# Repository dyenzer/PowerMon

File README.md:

#Power Monitor
Non-intrusive way to monitor the power consumed in your home

This repository contains the schematics and code for this project.
More details at https://hackaday.io/project/6700-home-power-usage-monitor
  
#Repository Contents
* **/Schematic** - Circuit diagram and PCB layout
  
#License Information
This project is released under <a href = "https://creativecommons.org/licenses/by-sa/4.0/">CC BY-SA 4.0</a>  
Original Design by Drew Yenzer

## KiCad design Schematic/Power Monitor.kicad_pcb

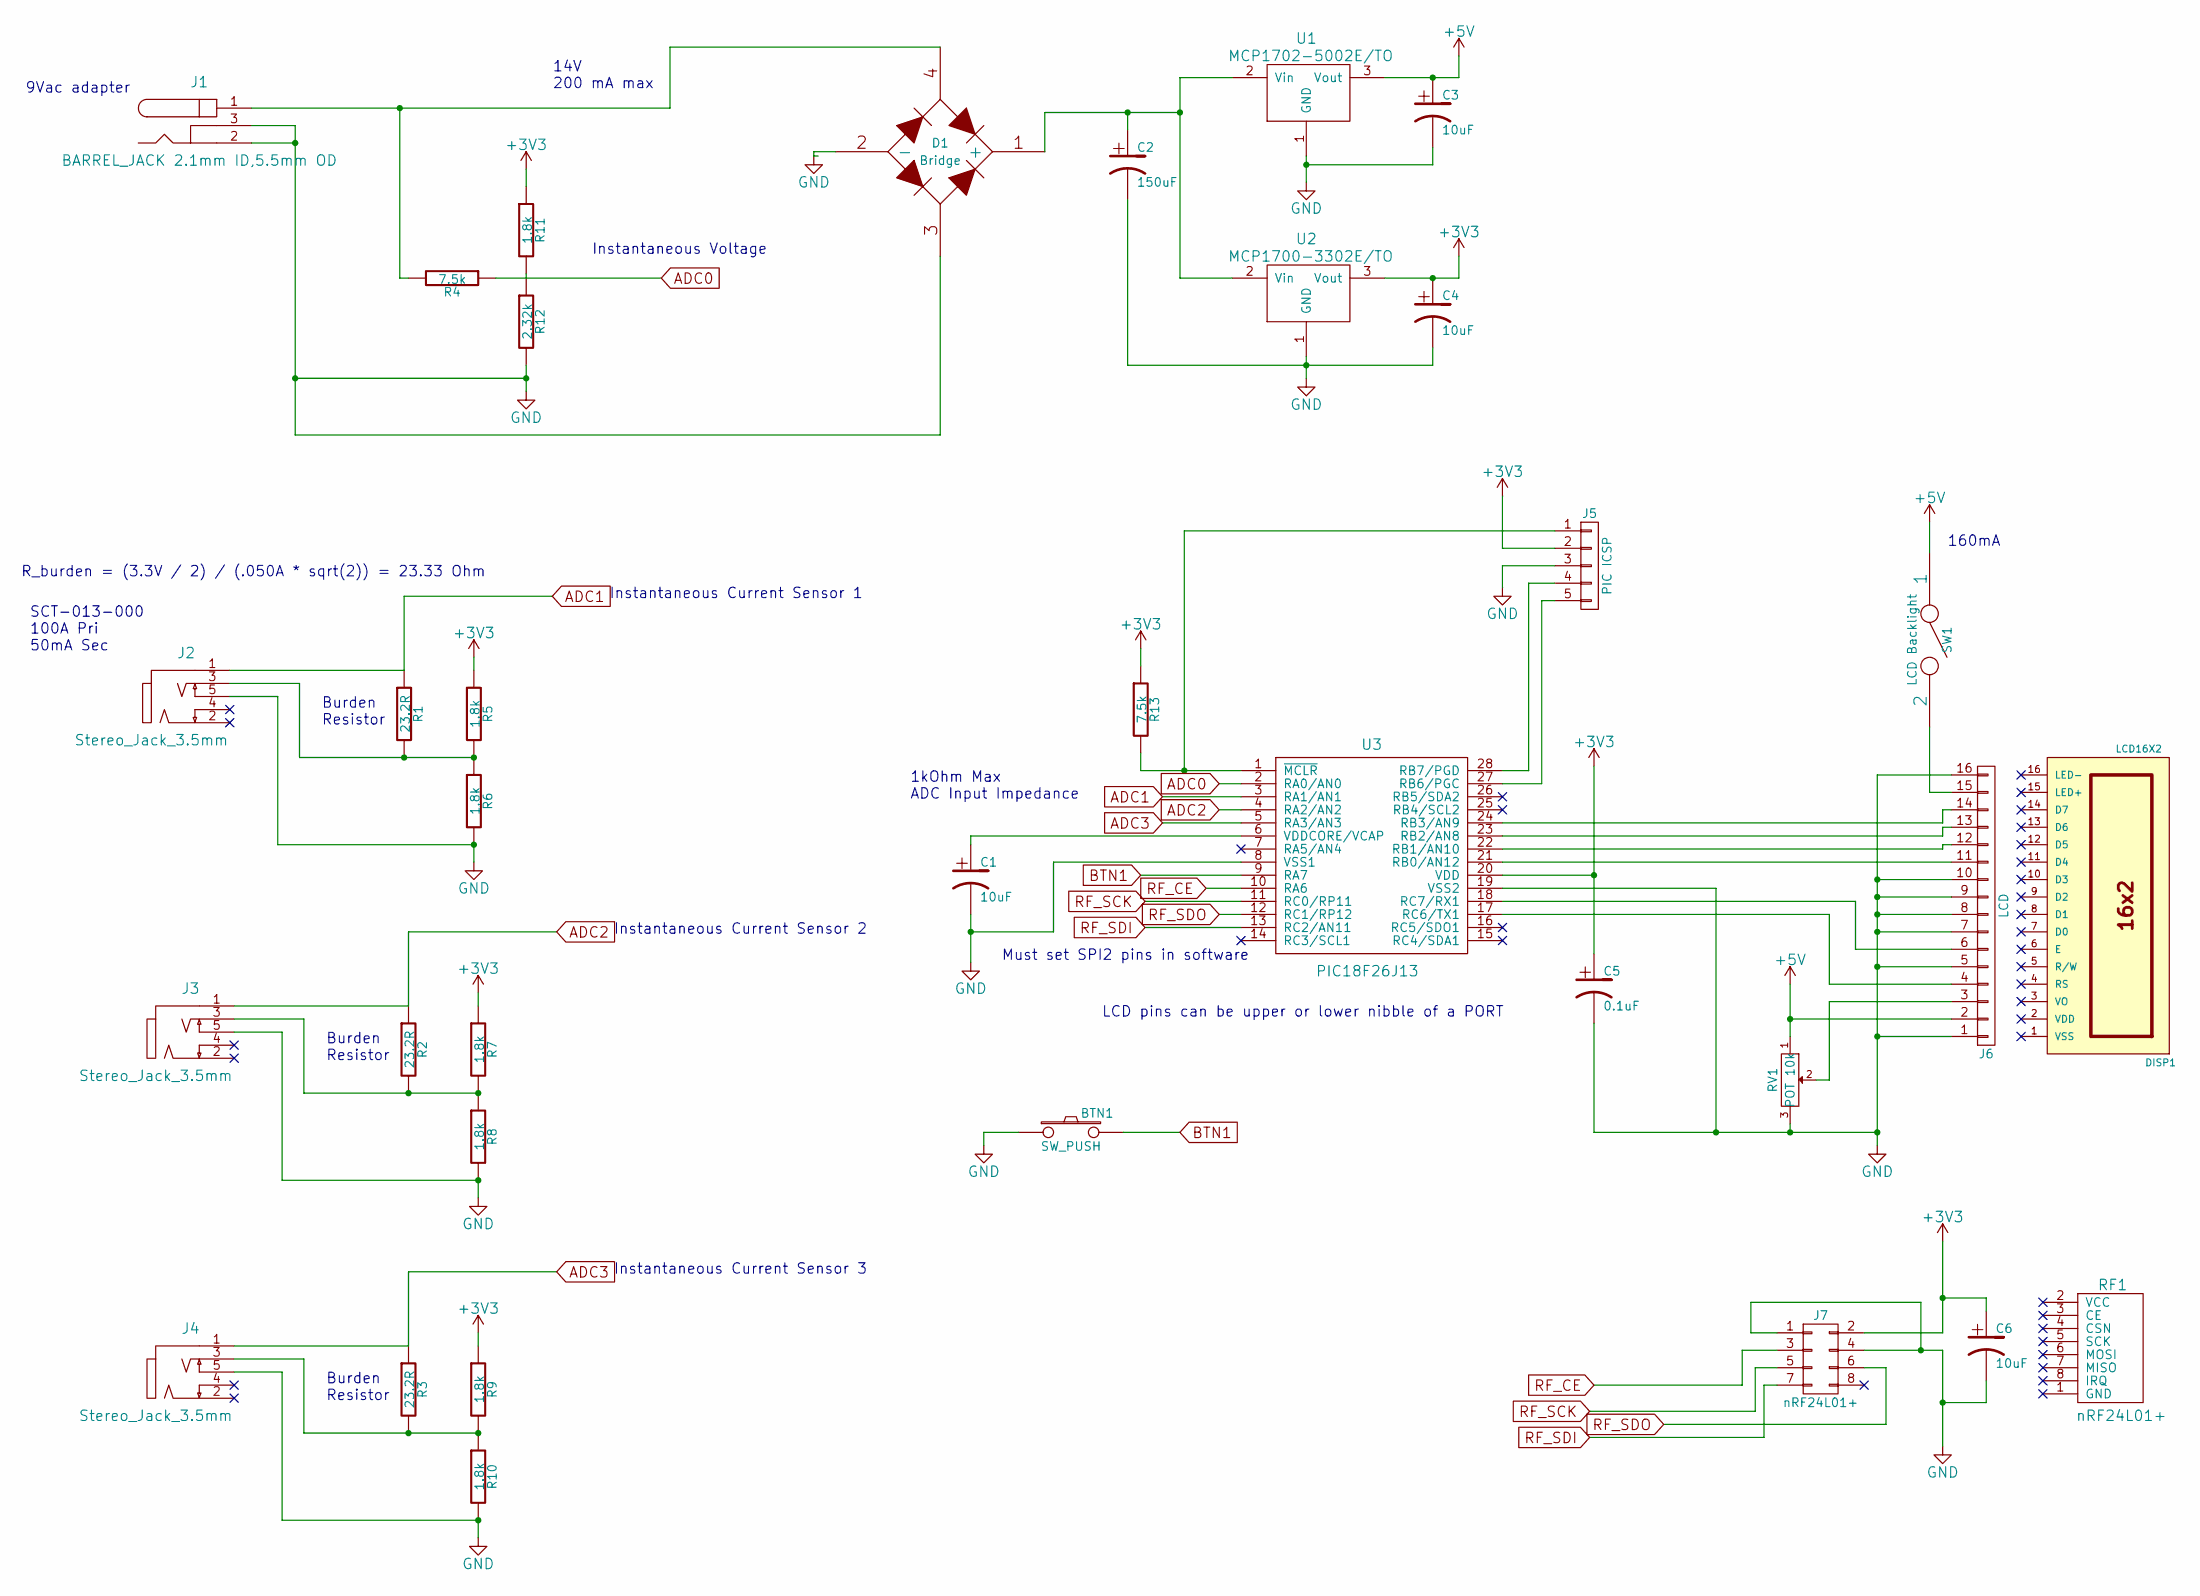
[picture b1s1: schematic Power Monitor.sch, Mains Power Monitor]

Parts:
BTN1: SW_PUSH; Pin_Header_Straight_1x02
C1, C3, C4, C6: 10uF; Capacitor3MMDiscRM2.5
C2: 150uF; Elko_vert_11.2x6.3mm_RM2.5
C5: 0.1uF; Capacitor3MMDiscRM2.5
D1: Bridge; Rectifier_SMT_TO-269AA
DISP1: LCD16X2; Dummy_Empty
J1: BARREL_JACK 2.1mm ID,5.5mm OD; Pin_Header_Straight_1x03
J2, J3, J4: Stereo_Jack_3.5mm; Stereo_Jack_3.5mm_2switch
J5: PIC ICSP; Pin_Header_Straight_1x05
J6: LCD; Conn_IDC_Header_TH_16pin
J7: nRF24L01+; Pin_Header_Straight_2x04
R1, R2, R3: 23.2R; R3
R4, R13: 7.5k; R2
R5, R6, R7, R8, R9, R10, R11: 1.8k; R2
R12: 2.32k; R2
RF1: nRF24L01+; Dummy_Empty
RV1: POT 10k; Potentiometer_Copal_CT-6EP
SW1: LCD Backlight; Pin_Header_Straight_1x02
U1: MCP1702-5002E/TO; TO-92-Free-inline-narrow-oval
U2: MCP1700-3302E/TO; TO-92-Free-inline-narrow-oval
U3: PIC18F26J13; SOIC-28_7.5x17.9mm_Pitch1.27mm

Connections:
+3V3: C4.1, C5.1, C6.1, J5.2, J7.2, R5.1, R7.1, R9.1, R11.1, R13.1, U2.3 (Vout), U3.20 (VDD)
+5V: C3.1, J6.2, RV1.1, SW1.1, U1.3 (Vout)
ADC0: R4.1, U3.2 (RA0/AN0)
ADC1: J2.1, R1.1, U3.3 (RA1/AN1)
ADC2: J3.1, R2.1, U3.4 (RA2/AN2)
ADC3: J4.1, R3.1, U3.5 (RA3/AN3)
BTN1: BTN1.2, U3.9 (RA7)
GND: BTN1.1, C1.2, C2.2, C3.2, C4.2, C5.2, C6.2, D1.2 (-), D1.3, J1.2, J1.3, J2.5, J3.5, J4.5, J5.3, J6.1, J6.5, J6.7, J6.8, J6.9, J6.10, J6.16, J7.1, J7.4, R6.2, R8.2, R10.2, R12.2, RV1.3, U1.1 (GND), U2.1 (GND), U3.8 (VSS1), U3.19 (VSS2)
unnamed: C1.1, U3.6 (VDDCORE/VCAP)
unnamed: C2.1, D1.1 (+), U1.2 (Vin), U2.2 (Vin)
unnamed: D1.4, J1.1, R4.2
unnamed: J2.3, R1.2, R5.2, R6.1
unnamed: J3.3, R2.2, R7.2, R8.1
unnamed: J4.3, R3.2, R9.2, R10.1
unnamed: J5.1, R13.2, U3.1 (~MCLR)
unnamed: J5.4, U3.28 (RB7/PGD)
unnamed: J5.5, U3.27 (RB6/PGC)
unnamed: J6.3, RV1.2
unnamed: J6.4, U3.17 (RC6/TX1)
unnamed: J6.6, U3.18 (RC7/RX1)
unnamed: J6.11, U3.21 (RB0/AN12)
unnamed: J6.12, U3.22 (RB1/AN10)
unnamed: J6.13, U3.23 (RB2/AN8)
unnamed: J6.14, U3.24 (RB3/AN9)
unnamed: J6.15, SW1.2
unnamed: R11.2, R12.1
RF_CE: J7.3, U3.10 (RA6)
RF_SCK: J7.5, U3.11 (RC0/RP11)
RF_SDI: J7.7, U3.13 (RC2/AN11)
RF_SDO: J7.6, U3.12 (RC1/RP12)

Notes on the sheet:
Burden Resistor
SCT-013-000 100A Pri 50mA Sec
R_burden = (3.3V / 2) / (.050A * sqrt(2)) = 23.33 Ohm
Must set SPI2 pins in software
LCD pins can be upper or lower nibble of a PORT
Instantaneous Voltage
Instantaneous Current Sensor 1
Instantaneous Current Sensor 2
Instantaneous Current Sensor 3
9Vac adapter
14V 200 mA max
160mA
1kOhm Max ADC Input Impedance

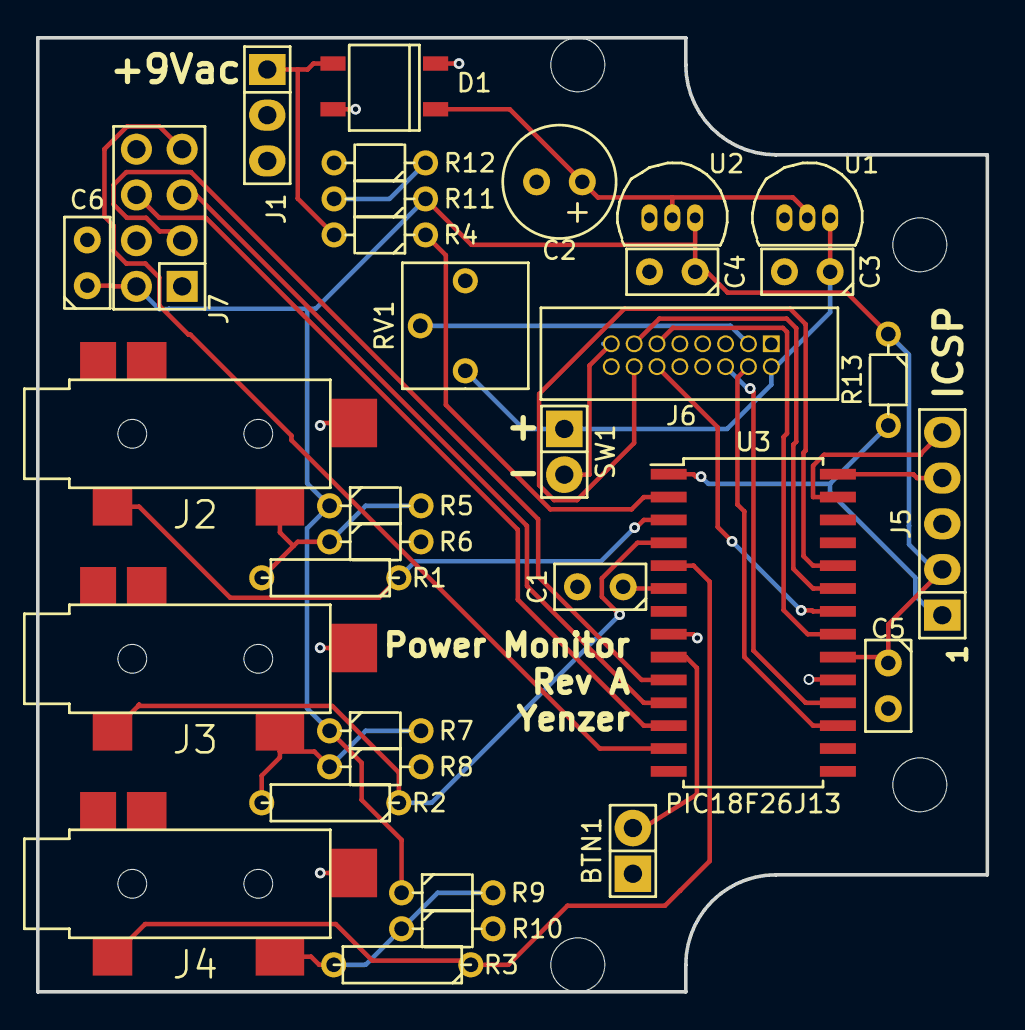
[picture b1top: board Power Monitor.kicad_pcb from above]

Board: 2 copper layers, 52.8 x 53.0 mm, 37 parts (0 on the bottom side), 30 nets.

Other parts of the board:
MountingHole1, MountingHole2, MountingHole3, MountingHole4: VAL**; MountingHole_3mm

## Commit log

2015-07-11 :lollipop: Added .gitattributes
2015-07-12 Initial add
2015-07-12 Modified format
